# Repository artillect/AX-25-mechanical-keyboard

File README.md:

# AX-25-mechanical-keyboard
 
This repository contains the KiCAD project files for my [Arduino/Raspberry Pi controlled typewriter project](https://github.com/artillect/serial-typewriter)

## Schematic

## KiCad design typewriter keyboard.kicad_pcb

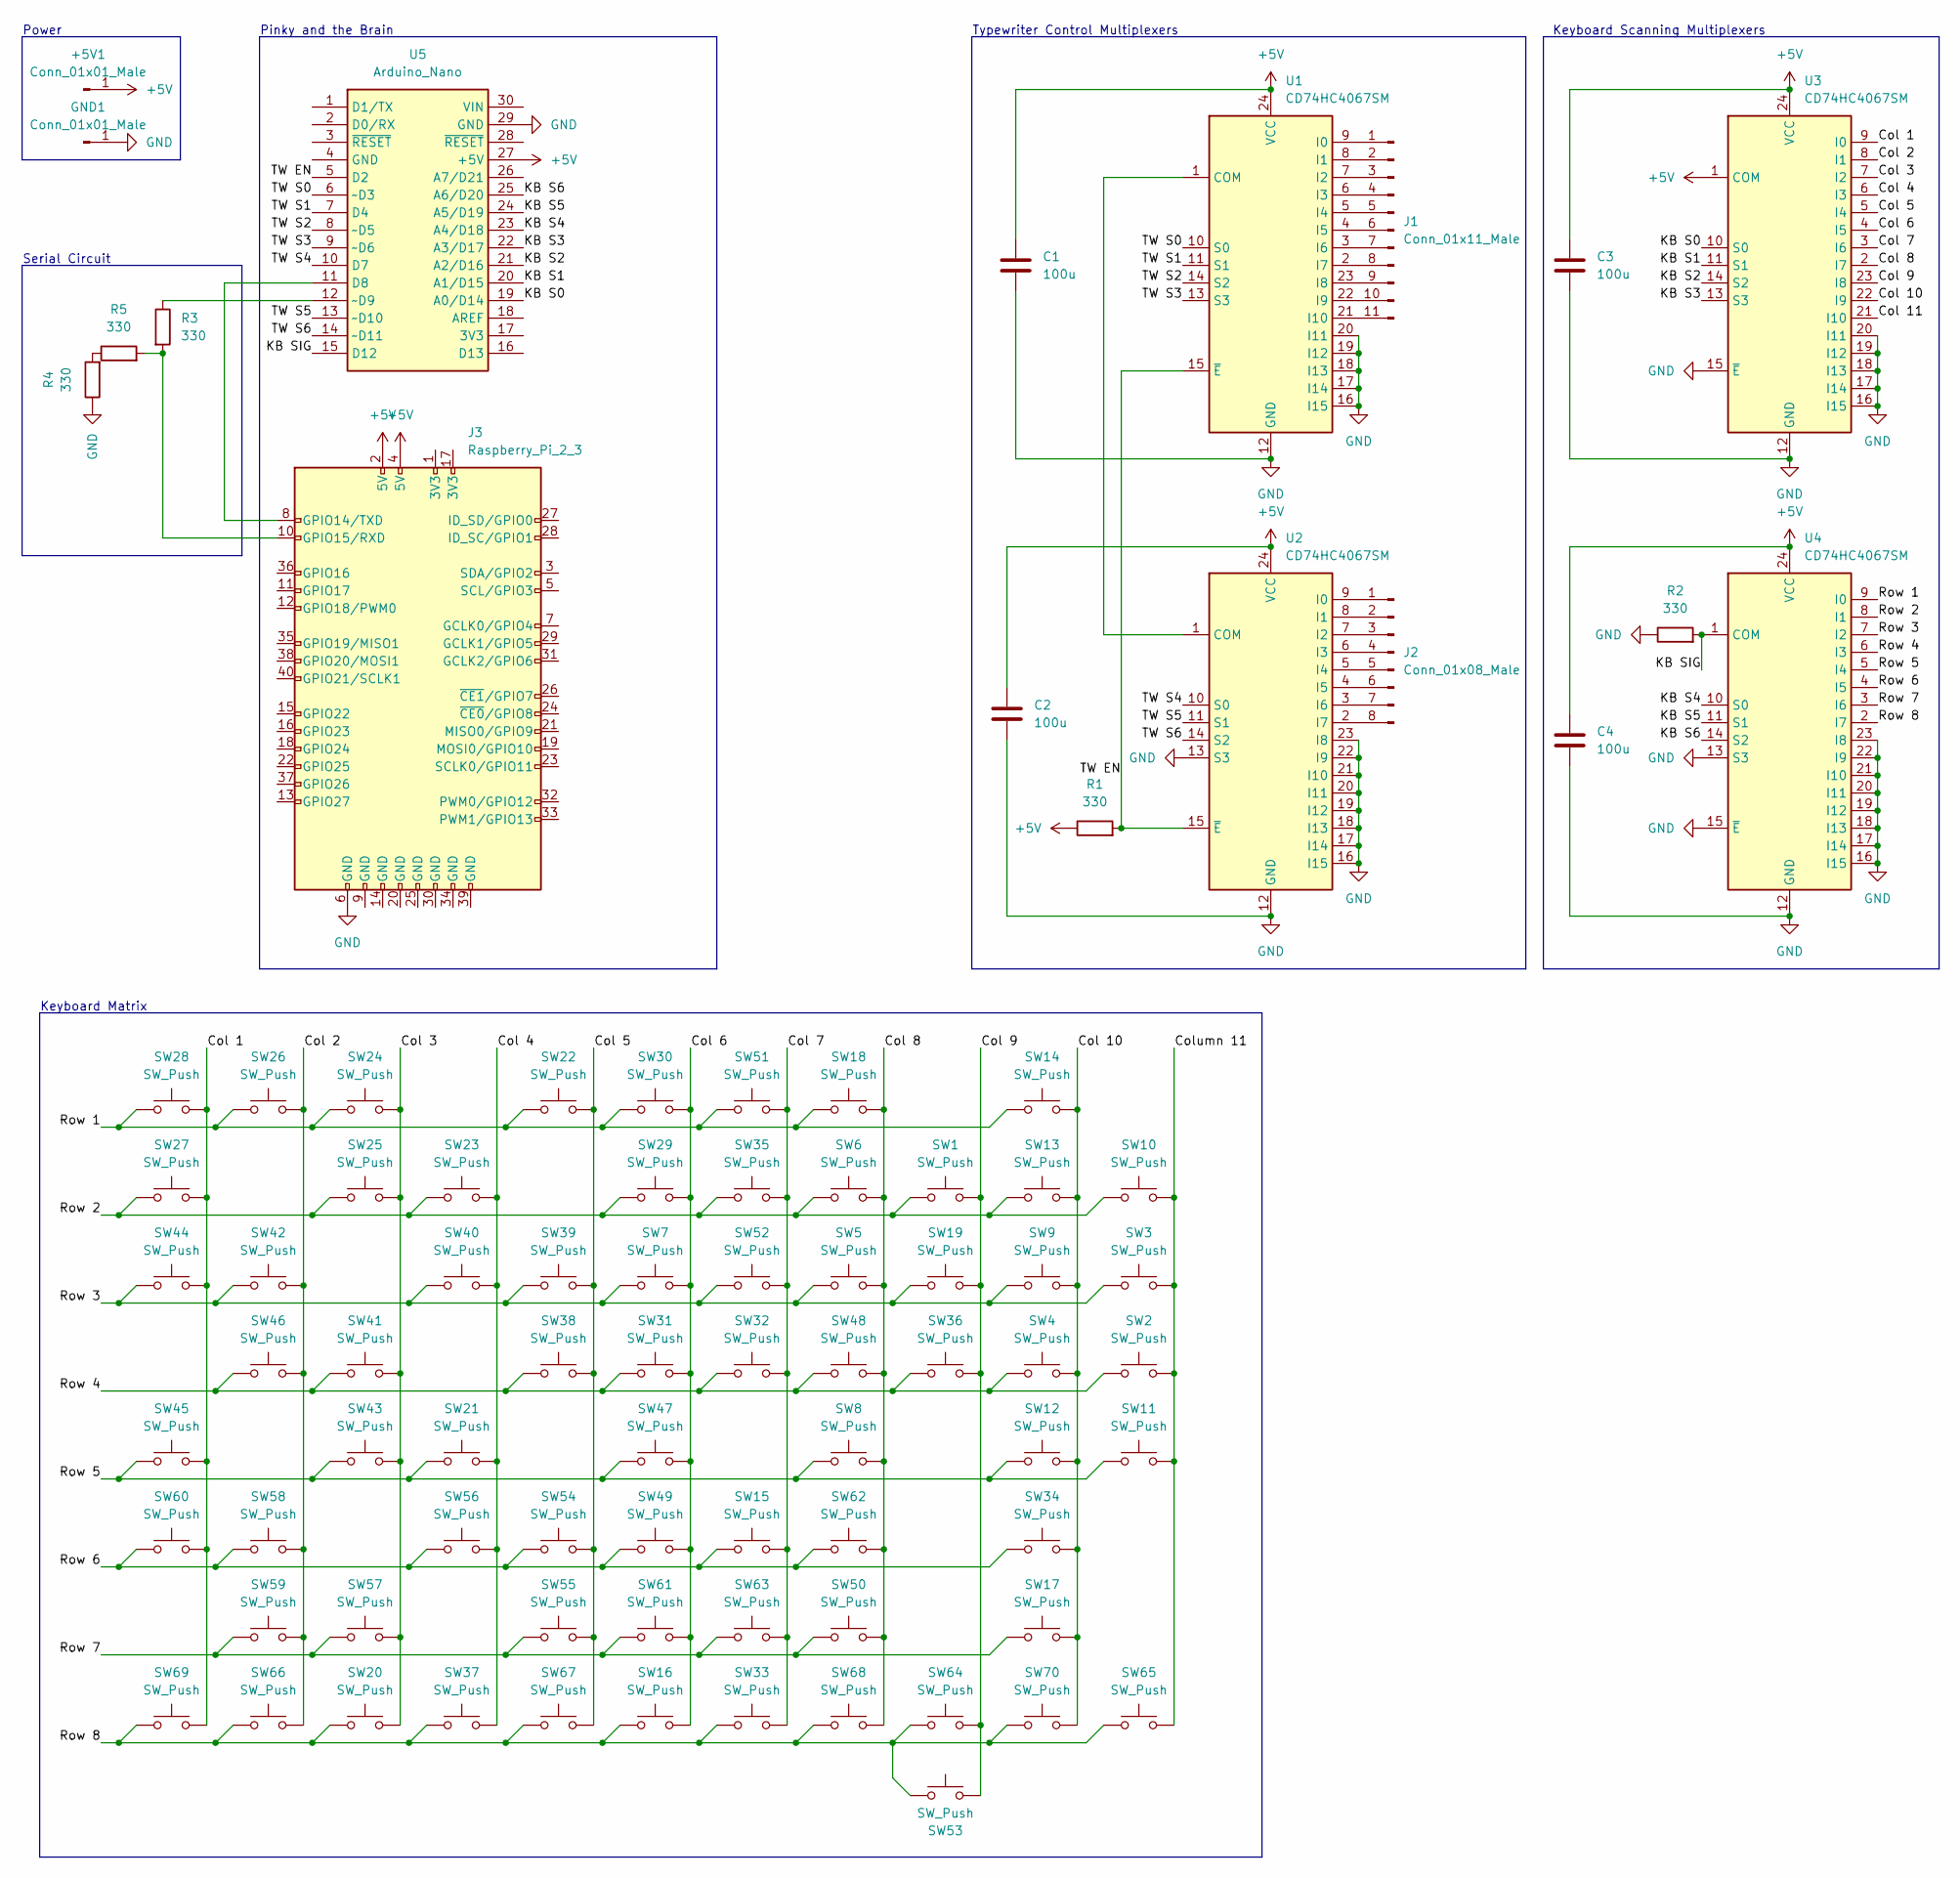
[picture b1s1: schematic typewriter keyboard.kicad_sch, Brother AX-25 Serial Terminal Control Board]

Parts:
+5V1: Conn_01x01_Male; SolderWire-0.25sqmm_1x01_D0.65mm_OD1.7mm
C1, C2, C3, C4: 100u; C_Disc_D3.4mm_W2.1mm_P2.50mm
GND1: Conn_01x01_Male; SolderWire-0.25sqmm_1x01_D0.65mm_OD1.7mm
J1: Conn_01x11_Male; PinHeader_1x11_P2.54mm_Vertical
J2: Conn_01x08_Male; PinHeader_1x08_P2.54mm_Vertical
J3: Raspberry_Pi_2_3; Raspberry_Pi_Zero_Socketed_THT_FaceDown_MountingHoles
R1, R2, R3, R4, R5: 330; R_Axial_DIN0207_L6.3mm_D2.5mm_P10.16mm_Horizontal
SW1, SW2, SW3, SW4, SW5, SW6, SW7, SW8, SW9, SW10, SW11, SW12, SW13, SW14, SW15, SW17, SW18, SW19, SW21, SW22, SW23, SW24, SW25, SW26, SW27, SW28, SW29, SW30, SW31, SW32, SW34, SW35, SW36, SW38, SW39, SW40, SW41, SW42, SW43, SW44, SW45, SW46, SW47, SW48, SW50, SW51, SW52, SW54, SW55, SW56, SW57, SW58, SW59, SW60, SW61, SW62, SW63, SW65: SW_Push; MX-1U-NoLED
SW16: SW_Push; MX-2U-NoLED
SW20, SW33: SW_Push; MX-1.5U-NoLED
SW37: SW_Push; MX-1.75U-NoLED
SW49, SW53: SW_Push; MX-2.25U-NoLED
SW64: SW_Push; MX-2.75U-NoLED
SW66, SW67, SW69, SW70: SW_Push; MX-1.25U-NoLED
SW68: SW_Push; MX-6.25U-NoLED
U1, U2, U3, U4: CD74HC4067SM; SSOP-24_5.3x8.2mm_P0.65mm
U5: Arduino_Nano

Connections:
+5V: +5V1.1, C1.1, C2.1, C3.1, C4.1, J3.2 (5V), J3.4 (5V), R1.1, U1.24 (VCC), U2.24 (VCC), U3.1 (COM), U3.24 (VCC), U4.24 (VCC), U5.27 (+5V)
/Col 1: SW27.2, SW28.2, SW44.2, SW45.2, SW60.2, SW69.2, U3.9 (I0)
/Col 2: SW26.2, SW42.2, SW46.2, SW58.2, SW59.2, SW66.2, U3.8 (I1)
/Col 3: SW20.2, SW24.2, SW25.2, SW41.2, SW43.2, SW57.2, U3.7 (I2)
/Col 4: SW21.2, SW23.2, SW37.2, SW40.2, SW56.2, U3.6 (I3)
/Col 5: SW22.2, SW38.2, SW39.2, SW54.2, SW55.2, SW67.2, U3.5 (I4)
/Col 6: SW7.2, SW16.2, SW29.2, SW30.2, SW31.2, SW47.2, SW49.2, SW61.2, U3.4 (I5)
/Col 7: SW15.2, SW32.2, SW33.2, SW35.2, SW51.2, SW52.2, SW63.2, U3.3 (I6)
/Col 8: SW5.2, SW6.2, SW8.2, SW18.2, SW48.2, SW50.2, SW62.2, SW68.2, U3.2 (I7)
/Col 9: SW1.2, SW19.2, SW36.2, SW53.1, SW64.2, U3.23 (I8)
/Col 10: SW4.2, SW9.2, SW12.2, SW13.2, SW14.2, SW17.2, SW34.2, SW70.2, U3.22 (I9)
/Col 11: U3.21 (I10)
/Column 11: SW2.2, SW3.2, SW10.2, SW11.2, SW65.2
/KB S0: U3.10 (S0), U5.19 (A0/D14)
/KB S1: U3.11 (S1), U5.20 (A1/D15)
/KB S2: U3.14 (S2), U5.21 (A2/D16)
/KB S3: U3.13 (S3), U5.22 (A3/D17)
/KB S4: U4.10 (S0), U5.23 (A4/D18)
/KB S5: U4.11 (S1), U5.24 (A5/D19)
/KB S6: U4.14 (S2), U5.25 (A6/D20)
/KB SIG: R2.2, U4.1 (COM), U5.15 (D12)
/Row 1: SW14.1, SW18.1, SW22.1, SW24.1, SW26.1, SW28.1, SW30.1, SW51.1, U4.9 (I0)
/Row 2: SW1.1, SW6.1, SW10.1, SW13.1, SW23.1, SW25.1, SW27.1, SW29.1, SW35.1, U4.8 (I1)
/Row 3: SW3.1, SW5.1, SW7.1, SW9.1, SW19.1, SW39.1, SW40.1, SW42.1, SW44.1, SW52.1, U4.7 (I2)
/Row 4: SW2.1, SW4.1, SW31.1, SW32.1, SW36.1, SW38.1, SW41.1, SW46.1, SW48.1, U4.6 (I3)
/Row 5: SW8.1, SW11.1, SW12.1, SW21.1, SW43.1, SW45.1, SW47.1, U4.5 (I4)
/Row 6: SW15.1, SW34.1, SW49.1, SW54.1, SW56.1, SW58.1, SW60.1, SW62.1, U4.4 (I5)
/Row 7: SW17.1, SW50.1, SW55.1, SW57.1, SW59.1, SW61.1, SW63.1, U4.3 (I6)
/Row 8: SW16.1, SW20.1, SW33.1, SW37.1, SW53.2, SW64.1, SW65.1, SW66.1, SW67.1, SW68.1, SW69.1, SW70.1, U4.2 (I7)
/TW EN: R1.2, U1.15 (~E), U2.15 (~E), U5.5 (D2)
/TW S0: U1.10 (S0), U5.6 (~D3)
/TW S1: U1.11 (S1), U5.7 (D4)
/TW S2: U1.14 (S2), U5.8 (~D5)
/TW S3: U1.13 (S3), U5.9 (~D6)
/TW S4: U2.10 (S0), U5.10 (D7)
/TW S5: U2.11 (S1), U5.13 (~D10)
/TW S6: U2.14 (S2), U5.14 (~D11)
GND: C1.2, C2.2, C3.2, C4.2, GND1.1, J3.6 (GND), R2.1, R4.1, U1.12 (GND), U1.16 (I15), U1.17 (I14), U1.18 (I13), U1.19 (I12), U1.20 (I11), U2.12 (GND), U2.13 (S3), U2.16 (I15), U2.17 (I14), U2.18 (I13), U2.19 (I12), U2.20 (I11), U2.21 (I10), U2.22 (I9), U2.23 (I8), U3.12 (GND), U3.15 (~E), U3.16 (I15), U3.17 (I14), U3.18 (I13), U3.19 (I12), U3.20 (I11), U4.12 (GND), U4.13 (S3), U4.15 (~E), U4.16 (I15), U4.17 (I14), U4.18 (I13), U4.19 (I12), U4.20 (I11), U4.21 (I10), U4.22 (I9), U4.23 (I8), U5.29 (GND)
unnamed: J1.1, U1.9 (I0)
unnamed: J1.2, U1.8 (I1)
unnamed: J1.3, U1.7 (I2)
unnamed: J1.4, U1.6 (I3)
unnamed: J1.5, U1.5 (I4)
unnamed: J1.6, U1.4 (I5)
unnamed: J1.7, U1.3 (I6)
unnamed: J1.8, U1.2 (I7)
unnamed: J1.9, U1.23 (I8)
unnamed: J1.10, U1.22 (I9)
unnamed: J1.11, U1.21 (I10)
unnamed: J2.1, U2.9 (I0)
unnamed: J2.2, U2.8 (I1)
unnamed: J2.3, U2.7 (I2)
unnamed: J2.4, U2.6 (I3)
unnamed: J2.5, U2.5 (I4)
unnamed: J2.6, U2.4 (I5)
unnamed: J2.7, U2.3 (I6)
unnamed: J2.8, U2.2 (I7)
unnamed: J3.8 (GPIO14/TXD), U5.11 (D8)
unnamed: J3.10 (GPIO15/RXD), R3.2, R5.2
unnamed: R3.1, U5.12 (~D9)
unnamed: R4.2, R5.1
unnamed: U1.1 (COM), U2.1 (COM)

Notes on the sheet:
Typewriter Control Multiplexers
Power
Pinky and the Brain
Keyboard Scanning Multiplexers
Keyboard Matrix
Serial Circuit

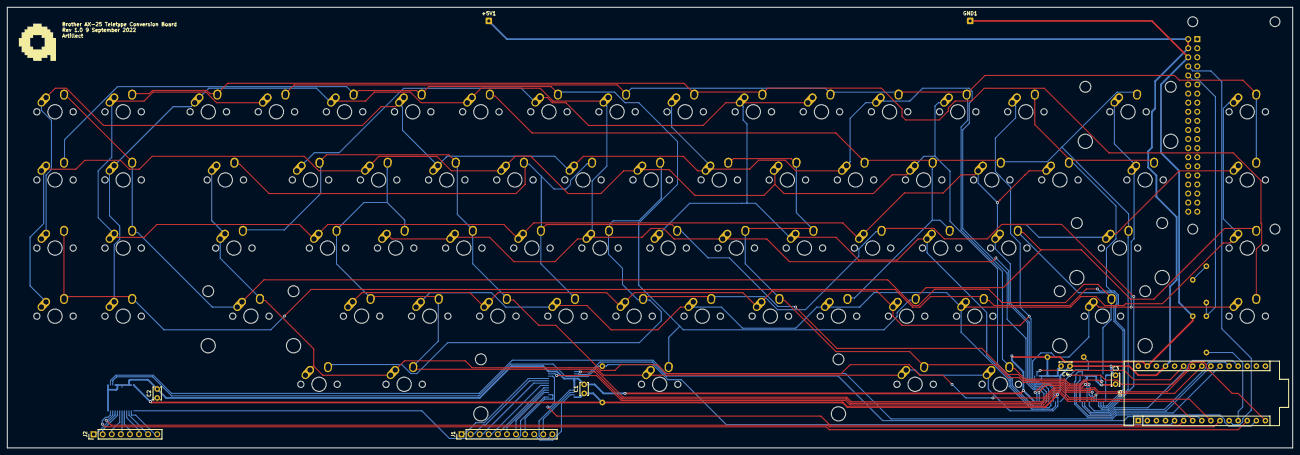
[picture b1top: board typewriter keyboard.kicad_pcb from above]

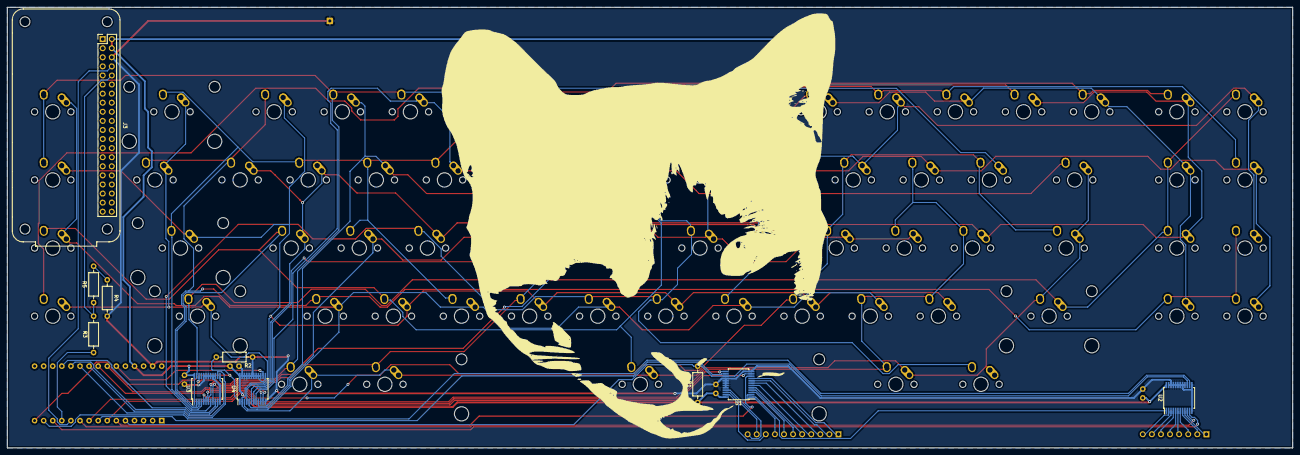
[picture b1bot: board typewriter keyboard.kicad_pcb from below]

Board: 2 copper layers, 359.4 x 123.2 mm, 89 parts (10 on the bottom side), 61 nets.

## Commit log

2022-09-08 Routed PCB, cleaned up schematic
2022-09-08 Cleaned up schematic and board
2022-09-10 Final changes for order
2022-09-10 Added schematic
2022-09-10 Added more file formats for schematic
2022-09-10 Added schematic to readme
